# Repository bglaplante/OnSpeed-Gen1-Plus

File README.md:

# OnSpeed-Gen1-Plus
Takes the original OnSpeed Gen1, ports to Arduino Mega

The original work at https://github.com/flyonspeed-org/OnSpeed-Gen1 used a $50 Due board.
I have ported the project to the Mega, which is sufficient as the Gaussian average was turned off.
This required changing timer libraries and a substantial rework of the code.

Currently as of August 2026, the project has been tested successfully with the Dynon D10A,
which means it works with that and the whole D100 series.

In addition it supports Skyview, and has been bench tested with a data generator emulating
Skyview data.

Garmin G3X is planned.

The project includes an LED display which shows the current reported AOA percent.
This simplifies configuration - you do a test flight at various slow flight speeds and record the reported AOA % values.
Then you can (post-flight) determine the starting thresholds for each OnSpeed point.
Those thresholds can then be placed onto an SD card.  When the system starts, it reads the SD card for configuration values.

A circuit board has been designed to hold the Mega Pro Mini, RS232 converter, LED display, SD card reader, and Step Down power supply.

Licensed under the NC-MIT 1.1 License. See LICENSE file in the project root.

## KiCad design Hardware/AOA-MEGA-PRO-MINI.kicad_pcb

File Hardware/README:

Version 0.2 circuit board is pending

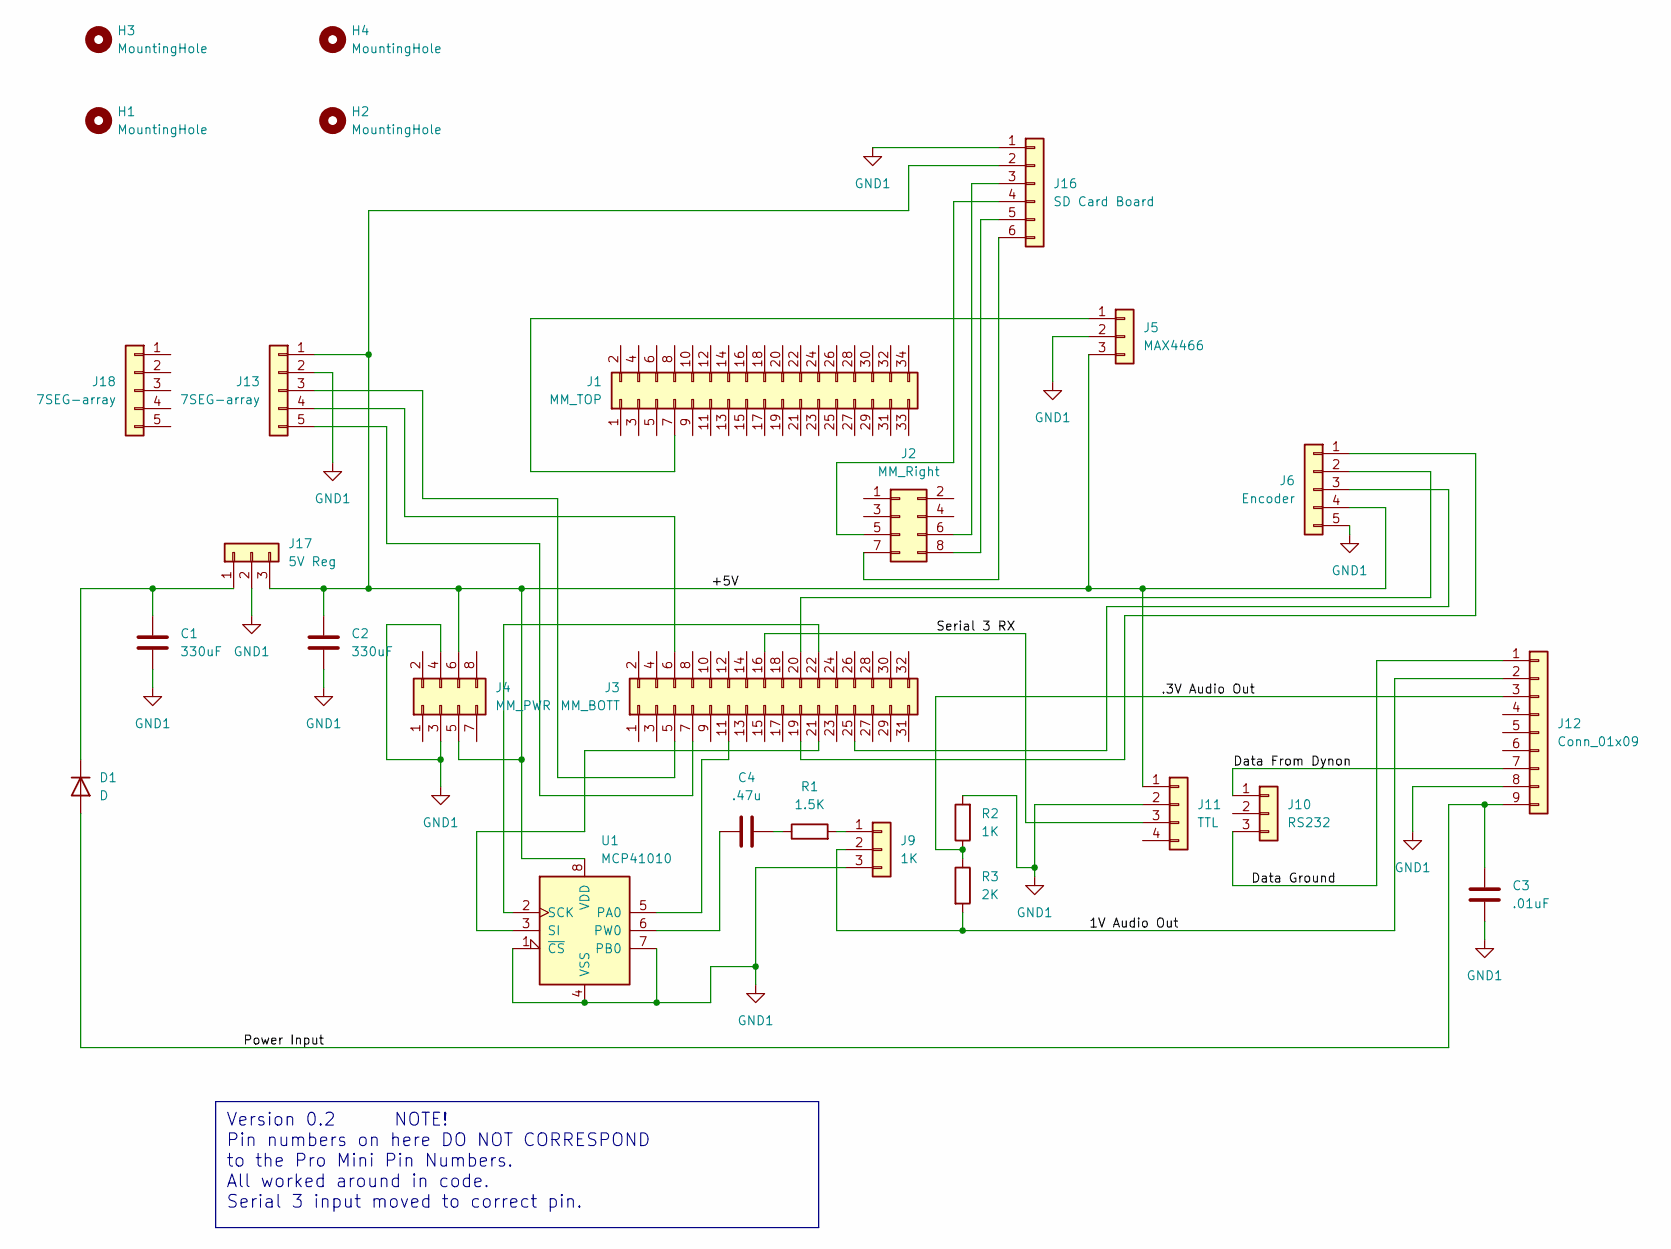
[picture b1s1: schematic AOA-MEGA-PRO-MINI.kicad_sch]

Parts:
C1, C2: 330uF; CP_Radial_D10.0mm_P5.00mm_P7.50mm
C3: .01uF; CP_Radial_D8.0mm_P5.00mm
C4: .47u; CP_Radial_D7.5mm_P2.50mm
D1: D; D_5W_P10.16mm_Horizontal
H1, H2, H3, H4: MountingHole; MountingHole_3.2mm_M3
J1: MM_TOP; PinSocket_2x17_P2.54mm_Vertical
J2: MM_Right; PinSocket_2x04_P2.54mm_Vertical
J3: MM_BOTT; PinSocket_2x16_P2.54mm_Vertical
J4: MM_PWR; PinSocket_2x04_P2.54mm_Vertical
J5: MAX4466; PinSocket_1x03_P2.54mm_Vertical
J6: Encoder; PinSocket_1x05_P2.54mm_Vertical
J9: 1K; PinSocket_1x03_P2.54mm_Vertical
J10: RS232; PinSocket_1x03_P2.54mm_Vertical
J11: TTL; PinSocket_1x04_P2.54mm_Vertical
J12: Conn_01x09; PinSocket_1x09_P2.54mm_Vertical
J13, J18: 7SEG-array; PinSocket_1x05_P2.54mm_Vertical
J16: SD Card Board; PinSocket_1x06_P2.54mm_Vertical
J17: 5V Reg; PinSocket_1x03_P2.54mm_Vertical
R1: 1.5K; R_1206_3216Metric
R2: 1K; R_1206_3216Metric
R3: 2K; R_1206_3216Metric
U1: MCP41010; DIP-8_W7.62mm

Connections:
/1V Audio Out: J9.2, J12.2, R3.2
/+5V: C2.1, J4.5, J4.6, J5.3, J6.4, J11.1, J13.1, J16.2, J17.3, U1.8 (VDD)
/.3V Audio Out: J12.3, R2.1, R3.1
/Data From Dynon: J10.1, J12.7
/Data Ground: J10.3, J12.1
/Power Input: C3.1, D1.2 (A), J12.9
/Serial 3 RX: J3.16, J11.3
GND1: C1.2, C2.2, C3.2, J4.3, J4.4, J5.2, J6.5, J9.3, J11.2, J12.8, J13.2, J16.1, J17.2, R2.2, U1.1 (~CS), U1.4 (VSS), U1.7 (PB0)
unnamed: C4.2, R1.1
unnamed: C1.1, D1.1 (K), J17.1
unnamed: J1.7, J5.1
unnamed: J3.11, U1.5 (PA0)
unnamed: J3.19, J6.1
unnamed: J3.20, J6.2
unnamed: J3.21, U1.3 (SI)
unnamed: J3.22, U1.2 (SCK)
unnamed: J3.25, J6.3
unnamed: J9.1, R1.2
unnamed: J3.5, J13.3
unnamed: J3.6, J13.4
unnamed: J3.7, J13.5
unnamed: J2.6, J16.3
unnamed: J2.5, J16.4
unnamed: J2.8, J16.5
unnamed: J2.7, J16.6
unnamed: C4.1, U1.6 (PW0)

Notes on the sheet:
Version 0.2 NOTE! Pin numbers on here DO NOT CORRESPOND to the Pro Mini Pin Numbers. All worked around in code. Serial 3 input moved to correct pin.

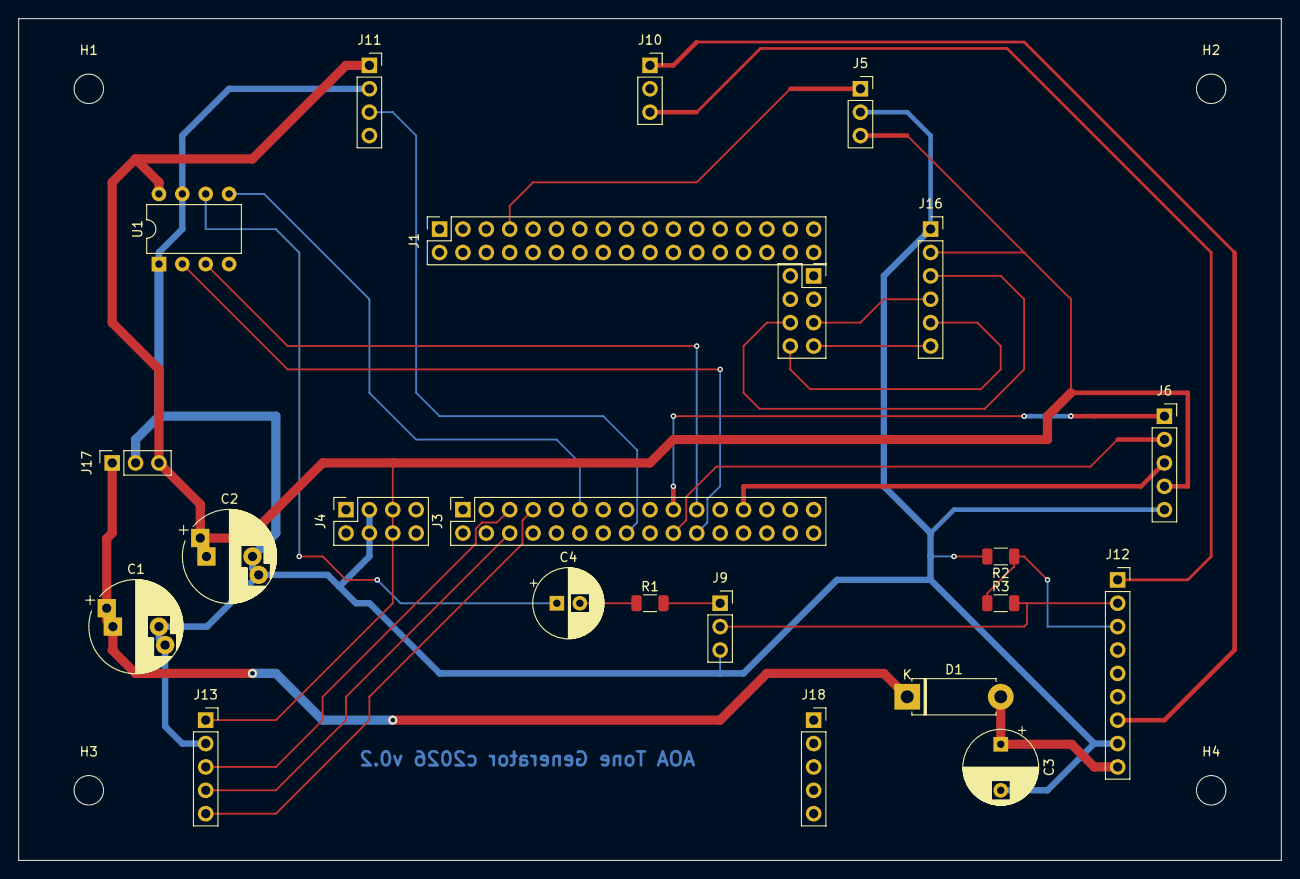
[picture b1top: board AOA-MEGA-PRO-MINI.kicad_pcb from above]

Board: 2 copper layers, 137.2 x 91.4 mm, 27 parts (0 on the bottom side), 26 nets.
